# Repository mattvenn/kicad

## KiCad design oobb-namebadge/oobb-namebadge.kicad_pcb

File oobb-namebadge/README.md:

# OOBB compatible SAO V.1.69bis name badge

* compatible with OOBB https://github.com/oomlout/oomlout-OOBB/wiki/pictureIndex
* 5 x [SAO V.1.69bis](https://hackaday.com/2019/03/20/introducing-the-shitty-add-on-v1-69bis-standard/) 6 pin connectors - GPIO1&2 shared across all connectors. I2C not connected
* pads for LiPo battery and USB charger
* 90x70mm $5 USD from https://pcbway.com
* [iCEBreaker](https://www.crowdsupply.com/1bitsquared/icebreaker-fpga) compatible. Red and Green LED output drive GPIO1&2 on all SAOs.

# BOM

* J5019 LiPo booster incorporating [TC4056A](docs/TC4056A.pdf) LiPo charger
* LiPo battery measuring 46x52mm
* 3.3v regulator [LD1117S33TR](https://uk.farnell.com/stmicroelectronics/ld1117s33tr/v-reg-ldo-3-3v-smd-1117-sot-223/dp/1202826)
* 2 x 10k pullup resistors if using iCEBreaker to control GPIOs
* sliding SMT switch [JS102012SAQN](https://uk.farnell.com/c-k-components/js102011saqn/switch-spdt-0-6a-6vdc-side-smd/dp/2320017)
* 5 x female 2x3 pin header with 2.54mm spacing, eg this [Pololu part](https://www.pololu.com/product/1023)

# Gerbers & Schematic

* [docs/schematic.pdf](docs/schematic.pdf)
* [oobb-namebadge-2019-10-10-fab.zip](oobb-namebadge-2019-10-10-fab.zip)

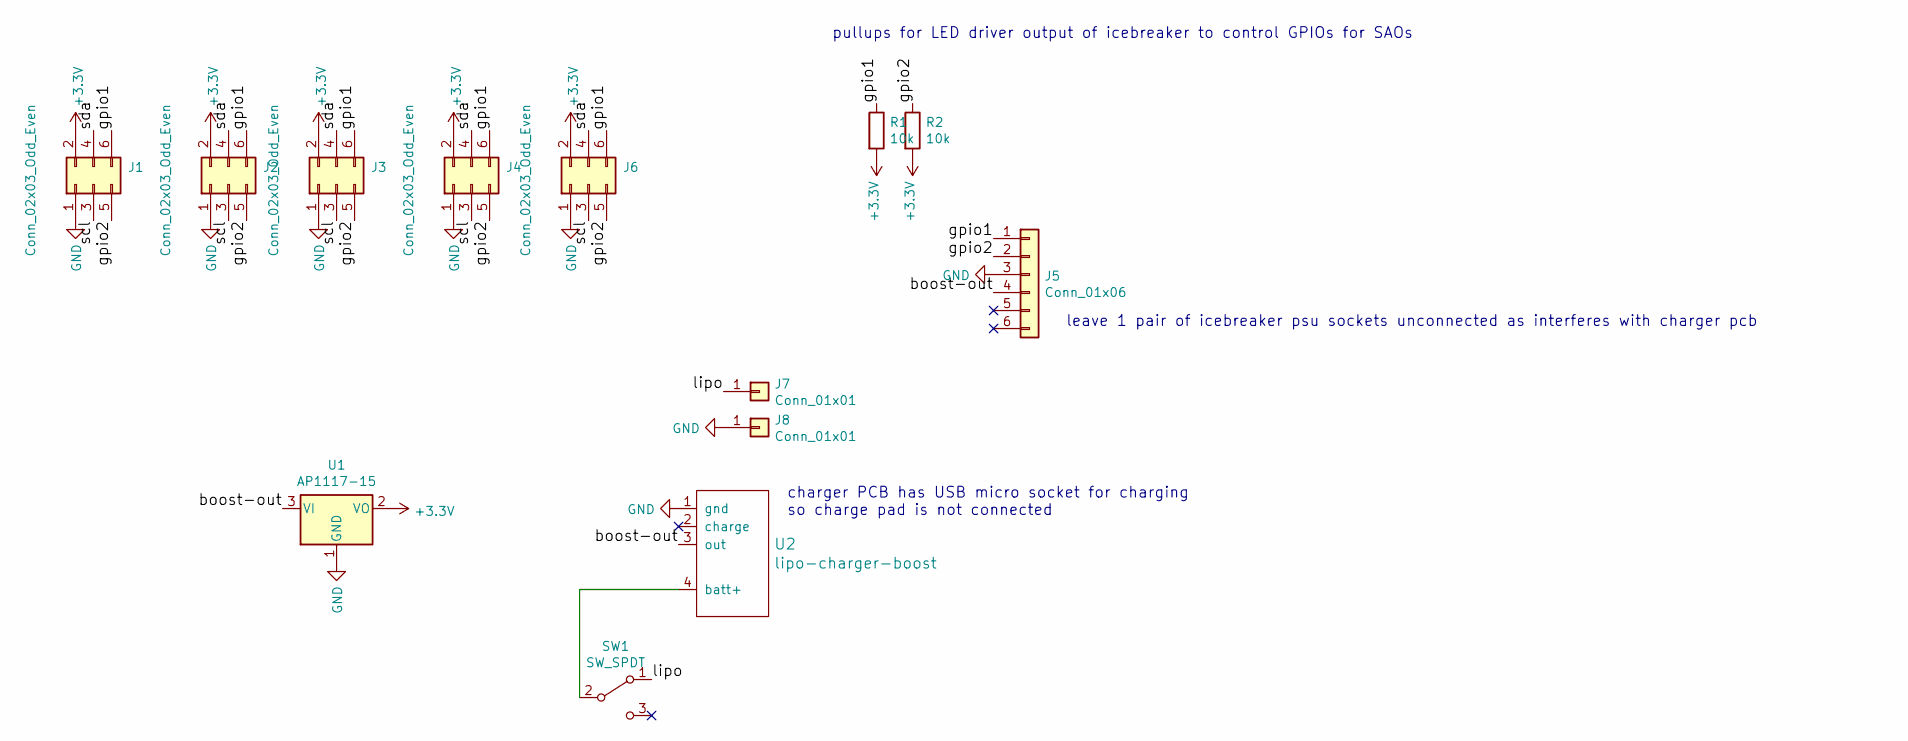
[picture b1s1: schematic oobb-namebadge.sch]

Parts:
J1, J2, J3, J4, J6: Conn_02x03_Odd_Even; Pin_Header_Straight_2x03_Pitch2.54mm
J5: Conn_01x06; icebreaker
J7, J8: Conn_01x01; Measurement_Point_Square-SMD-Pad_Big
R1, R2: 10k; R_0805_HandSoldering
SW1: SW_SPDT; SW_SPDT_CK-JS102011SAQN; farnell # 2320017
U1: AP1117-15; SOT-223; farnell # 1202826
U2: lipo-charger-boost

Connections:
+3V3: J1.2, J2.2, J3.2, J4.2, J6.2, R1.2, R2.2, U1.2 (VO)
/boost-out: J5.4, U1.3 (VI), U2.3 (out)
/gpio1: J1.6, J2.6, J3.6, J4.6, J5.1, J6.6, R1.1
/gpio2: J1.5, J2.5, J3.5, J4.5, J5.2, J6.5, R2.1
/lipo: J7.1, SW1.1 (A)
/scl: J1.3, J2.3, J3.3, J4.3, J6.3
/sda: J1.4, J2.4, J3.4, J4.4, J6.4
GND: J1.1, J2.1, J3.1, J4.1, J5.3, J6.1, J8.1, U1.1 (GND), U2.1 (gnd)
unnamed: SW1.2 (B), U2.4 (batt+)

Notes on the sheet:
charger PCB has USB micro socket for charging so charge pad is not connected
leave 1 pair of icebreaker psu sockets unconnected as interferes with charger pcb
pullups for LED driver output of icebreaker to control GPIOs for SAOs

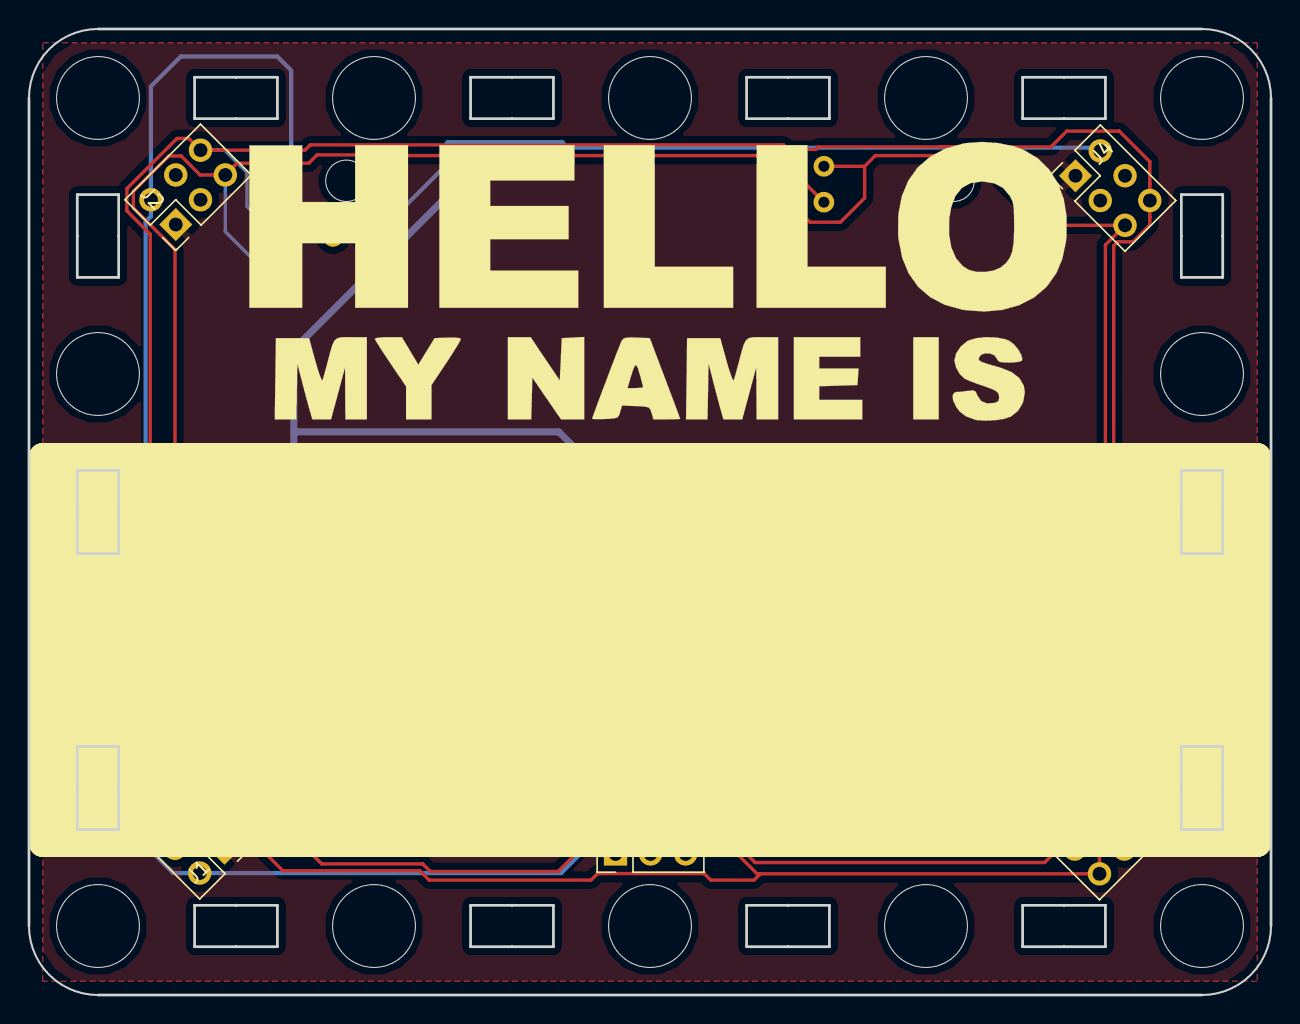
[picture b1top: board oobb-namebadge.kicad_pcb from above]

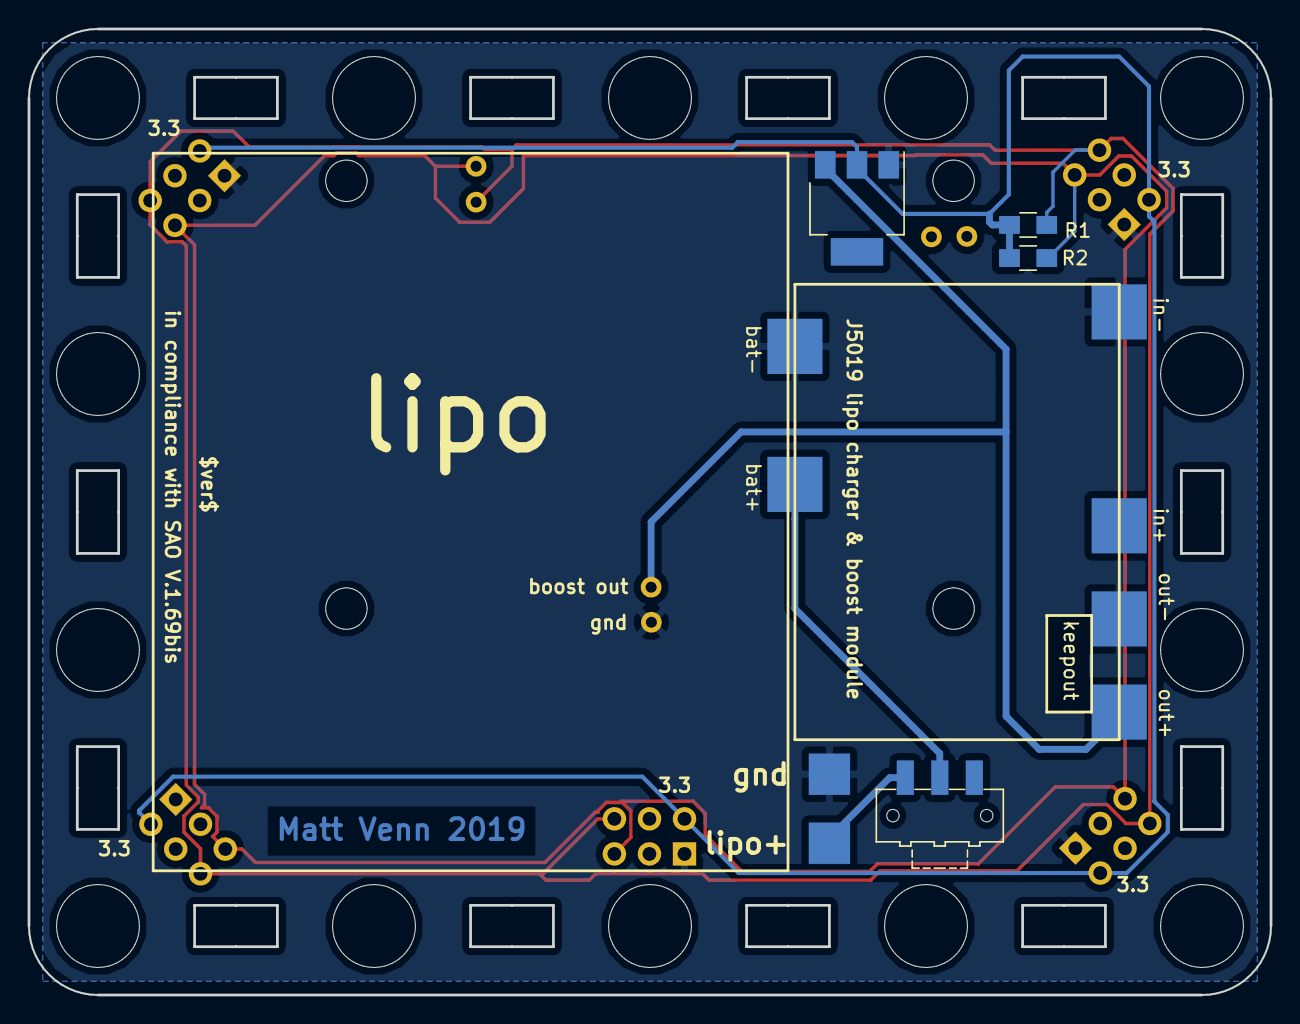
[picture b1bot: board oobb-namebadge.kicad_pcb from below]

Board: 2 copper layers, 90.0 x 70.0 mm, 13 parts (7 on the bottom side), 9 nets.

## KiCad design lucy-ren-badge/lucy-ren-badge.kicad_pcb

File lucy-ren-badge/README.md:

1300 dpi to convert from Rachel file to 71x51mm badge
$63 for 100 from pcbway

mask - normal then edit file to change layer
silk - invert
copper - invert then edit file
outline - fill black, export png, import inkscape, path->trace outline, scale 5.66, export DXF

reduced size of master image by 4 to 1008x756

BOM

pins - TODO!
slide switch - farnell
battery - ordered amazon
battery holder - farnell
attiny - check footprint & parts I have - done is correct
0.1u x 1  - farnell
1u x 1 - dnp
10k x 1 - farnell
60R x 1 - farnell

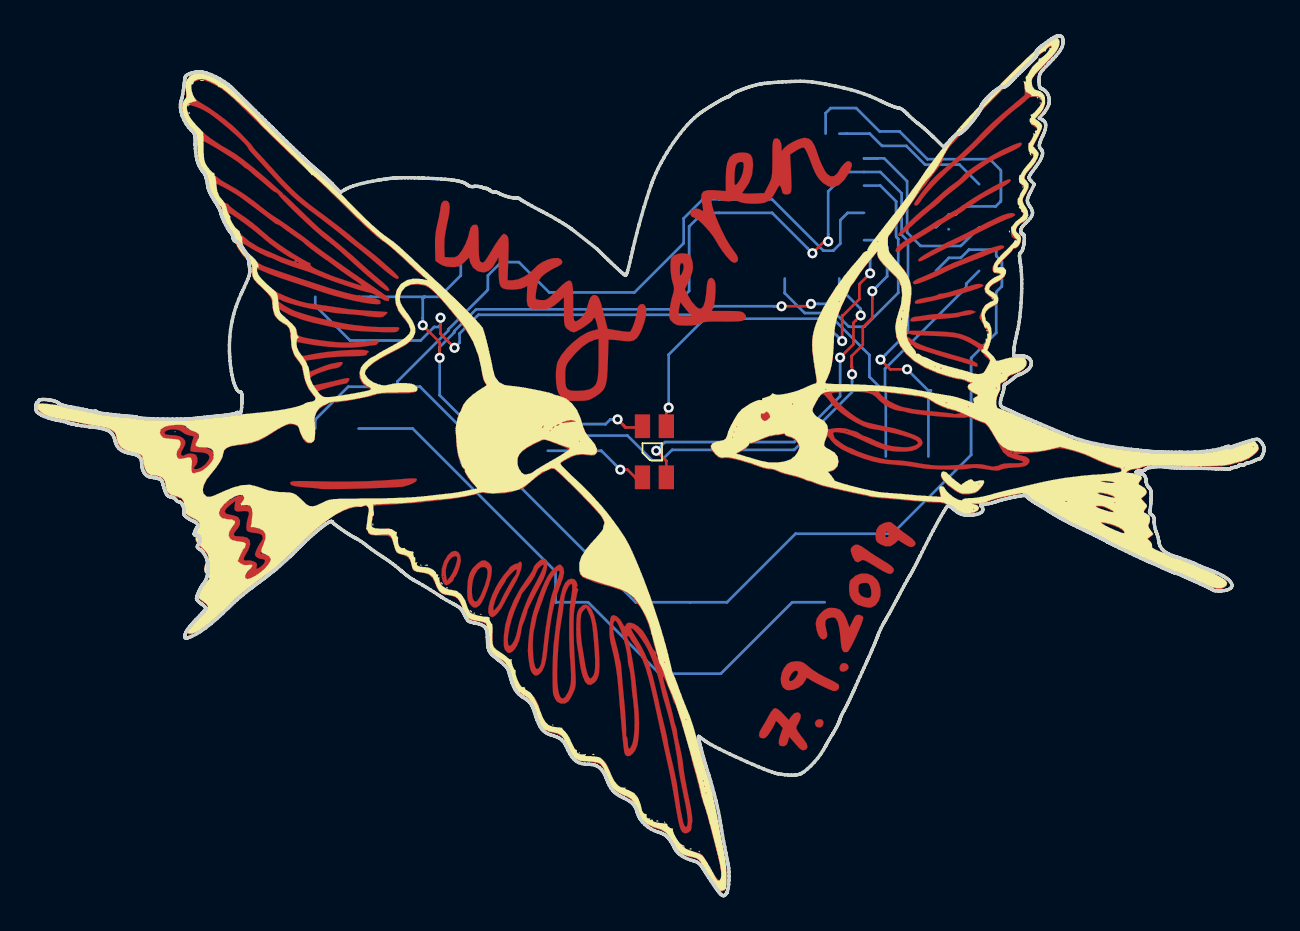
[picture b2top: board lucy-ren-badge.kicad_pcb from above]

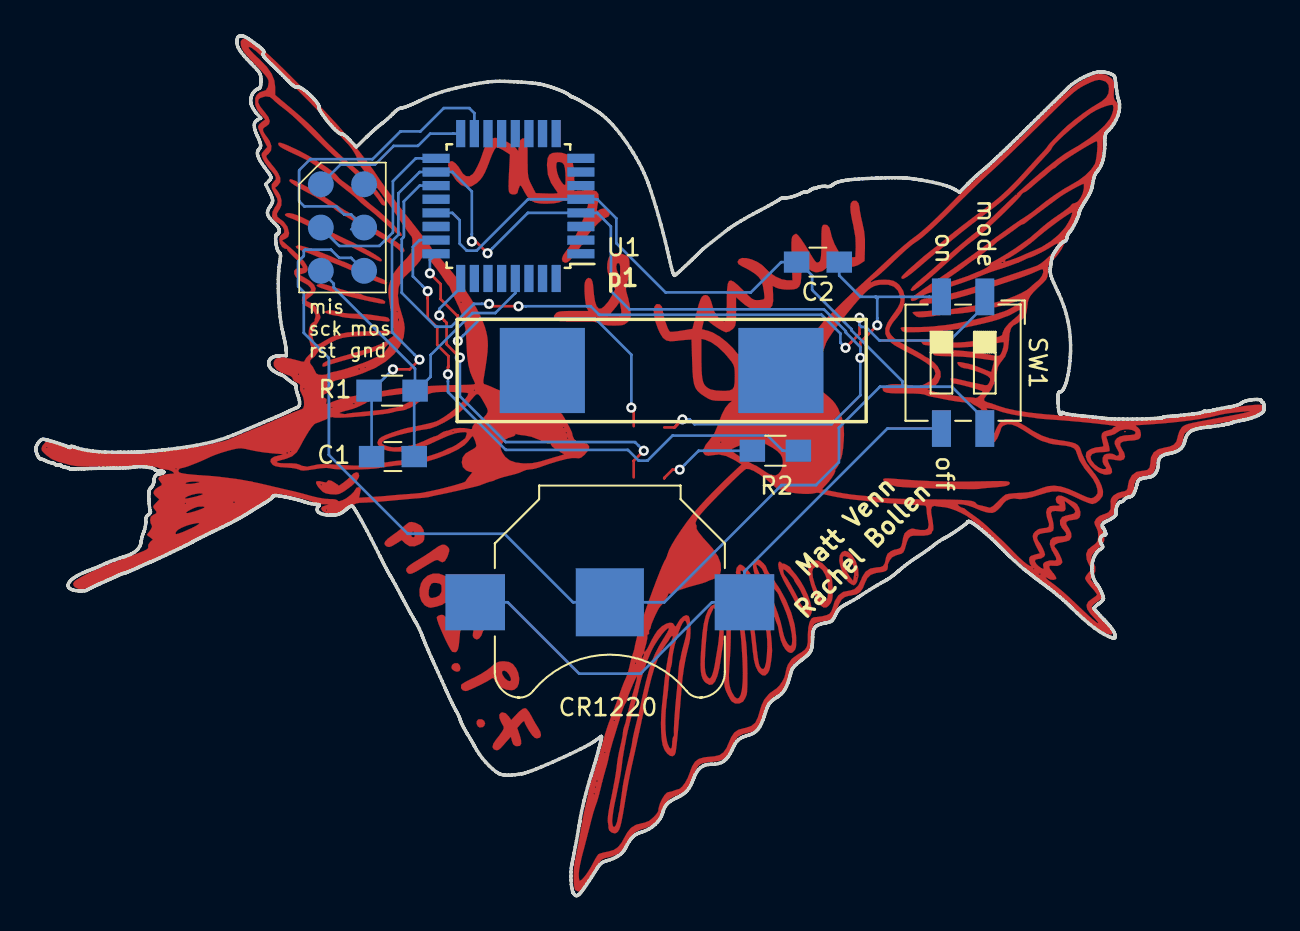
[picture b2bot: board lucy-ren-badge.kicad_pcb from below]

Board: 2 copper layers, 72.1 x 50.5 mm, 9 parts (8 on the bottom side), 12 nets.

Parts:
C1, C2: C; C_0805_HandSoldering
CR1220: Battery_Cell; Keystone_3000_1x12mm-CoinCell
J1: Conn_02x03_Odd_Even; icsp-2.54-smt
R1, R2: R; R_0805_HandSoldering
SW1: SW_DIP_x02; SW_DIP_SPSTx02_Slide_6.7x6.64mm_W6.73mm_P2.54mm_LowProfile_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
U1: ATTINY88-AU; TQFP-32_7x7mm_Pitch0.8mm
U2: rgbled; 3528-4p

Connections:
/b1: U1.25, U2.6
/g1: U1.24, U2.4
/miso: J1.1, U1.16
/mode: SW1.1, U1.19
/mosi: J1.4, U1.15
/r1: R2.2, U2.5
/reset: C1.2, J1.5, R1.1, U1.29
/sck: J1.3, U1.17
GND: C2.2, CR1220.2, J1.6, SW1.4, U1.5, U1.21
unnamed: CR1220.1, SW1.3
unnamed: R2.1, U1.23
VCC: C1.1, C2.1, R1.2, SW1.2, U1.4, U1.18, U2.1

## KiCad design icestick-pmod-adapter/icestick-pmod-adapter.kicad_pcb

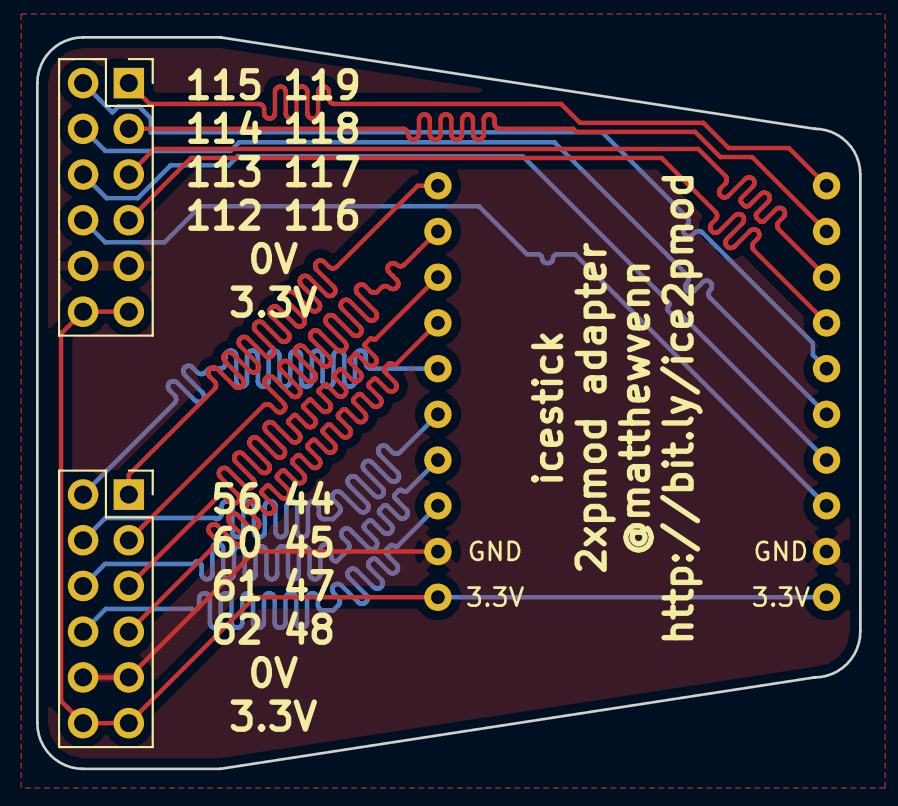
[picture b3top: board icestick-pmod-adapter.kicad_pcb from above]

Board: 2 copper layers, 45.7 x 40.6 mm, 3 parts (0 on the bottom side), 18 nets.

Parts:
J1, J2: Conn_02x06_Odd_Even; PinSocket_2x06_P2.54mm_Vertical
U1: icestick

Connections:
+3V3: J1.11, J1.12, J2.11, J2.12, U1.10, U1.20
/pmod44: J1.1, U1.1
/pmod45: J1.3, U1.2
/pmod47: J1.5, U1.3
/pmod48: J1.7, U1.4
/pmod56: J1.2, U1.5
/pmod60: J1.4, U1.6
/pmod61: J1.6, U1.7
/pmod62: J1.8, U1.8
/pmod112: J2.8, U1.18
/pmod113: J2.6, U1.17
/pmod114: J2.4, U1.16
/pmod115: J2.2, U1.15
/pmod116: J2.7, U1.14
/pmod117: J2.5, U1.13
/pmod118: J2.3, U1.12
/pmod119: J2.1, U1.11
GND: J1.9, J1.10, J2.9, J2.10, U1.9, U1.19

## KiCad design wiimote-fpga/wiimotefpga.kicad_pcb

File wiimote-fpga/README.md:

# breakout board for pixart IR camera used in wiimote

* PMOD interface.
* reset should be high for camera to run
* either use 25MHz onboard oscillator or supply 25MHz on clk pin

# bugs

* mixed sda and scl labels (fixed)
* crystal footprint was reversed (fixed)

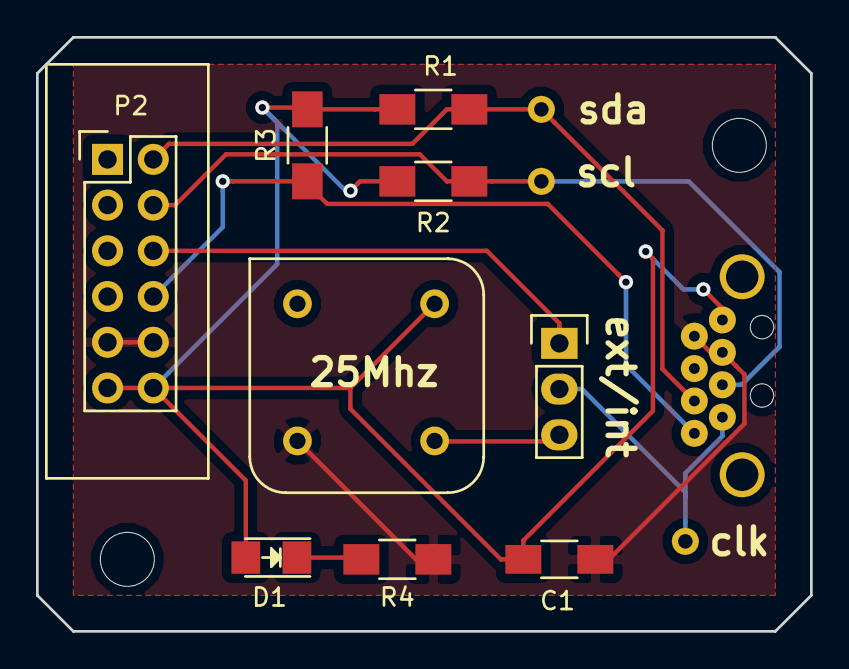
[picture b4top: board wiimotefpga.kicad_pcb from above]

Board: 2 copper layers, 43.0 x 33.0 mm, 13 parts (0 on the bottom side), 9 nets.

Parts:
C1: C; C_1206_HandSoldering
D1: LED; LED-1206
P1: CONN_01X03; Pin_Header_Straight_1x03
P2: CONN_02X06; Pin_Header_Straight_2x06
R1: R; R_1206_HandSoldering
R2: 4.7k; R_1206_HandSoldering
R3: 10k; R_1206_HandSoldering
R4: 150R; R_1206_HandSoldering
U1: oscillator
U2: wiimote-camera; wiimote
W1, W2, W3: TEST_1P; Measurement_Point_Round-TH_Small

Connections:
/cam_clk: P1.2, U2.7, W3.1
/clk: P1.1, P2.6
/osc: P1.3, U1.5
/reset: P2.8, R3.1, U2.8
/scl: P2.4, R2.1, U2.5, W2.1
/sda: P2.2, R1.1, U2.6, W1.1
GND: C1.2, P2.9, P2.10, R4.2, U1.4, U2.2, U2.3
unnamed: D1.1, R4.1
VCC: C1.1, D1.2, P2.11, P2.12, R1.2, R2.2, R3.2, U1.8, U2.1

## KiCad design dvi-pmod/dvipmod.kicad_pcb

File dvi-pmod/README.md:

# Minimal PMOD to DVI-D adapter

For FPGAs with no TMDS, trying to use AC coupled LVDS.
AC coupling suggested in this discussion:

http://electronics.stackexchange.com/questions/130942/transmitting-hdmi-dvi-over-an-fpga-with-no-support-for-tmds

# Status

* tested pattern at 640 x 480 @ 60Hz
* total pixels is 800 x 525 @ 60Hz = 25.2Mhz = 39.6ns

[pictures](https://goo.gl/photos/ScRRi142sbwstPGr6)

# Schematic

# Board

# Todo

* too close trace to g resistor, bridged when soldering

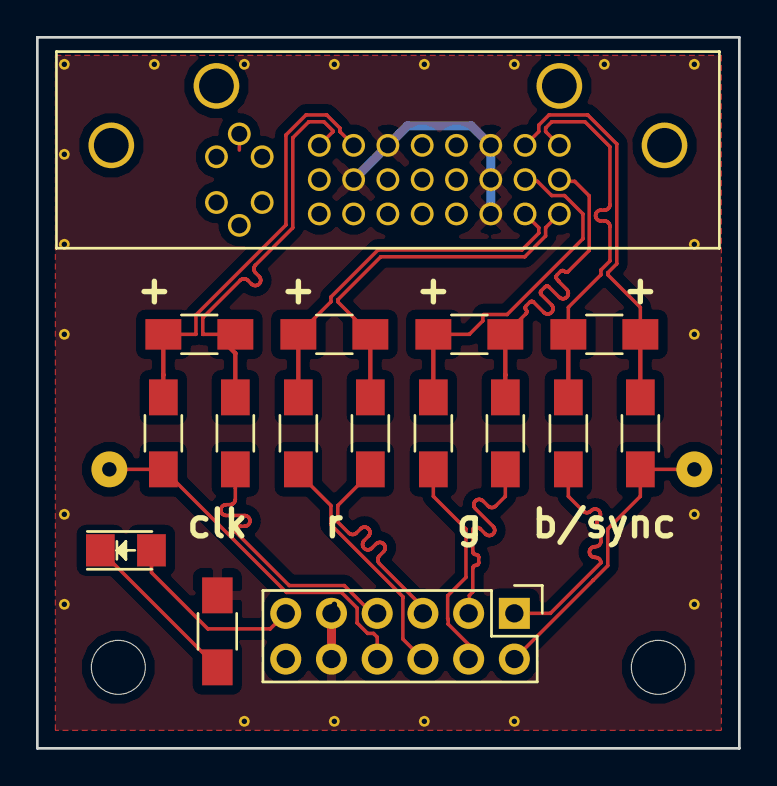
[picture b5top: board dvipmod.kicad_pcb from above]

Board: 2 copper layers, 39.0 x 39.5 mm, 18 parts (0 on the bottom side), 19 nets.

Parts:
C1, C2, C3, C4, C5, C6, C7, C8: C; C_1206_HandSoldering
D1: LED; LED-1206
P1: CONN_02X06; Pin_Header_Straight_2x06
R1, R2, R3, R4, R5: R; R_1206_HandSoldering
U1: dvi; molex dvi ra
W6, W8: TEST_1P; SolderWirePad_single_0-8mmDrill

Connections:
/b+: C6.2, P1.2, W6.1
/b-: C5.2, P1.1
/blue+: C6.1, R3.2, U1.18
/blue-: C5.1, R3.1, U1.17
/c+: C8.2, P1.8, W8.1
/c-: C7.2, P1.7
/clock+: C8.1, R4.2, U1.23
/clock-: C7.1, R4.1, U1.24
/g+: C4.2, P1.4
/g-: C3.2, P1.3
/green+: C4.1, R2.2, U1.10
/green-: C3.1, R2.1, U1.9
/r+: C2.2, P1.6
/r-: C1.2, P1.5
/red+: C2.1, R1.2, U1.2
/red-: C1.1, R1.1, U1.1
Earth: P1.9, P1.10, R5.2, U1.3, U1.11, U1.15, U1.19, U1.22
unnamed: D1.1, R5.1
VCC: D1.2, P1.11, P1.12

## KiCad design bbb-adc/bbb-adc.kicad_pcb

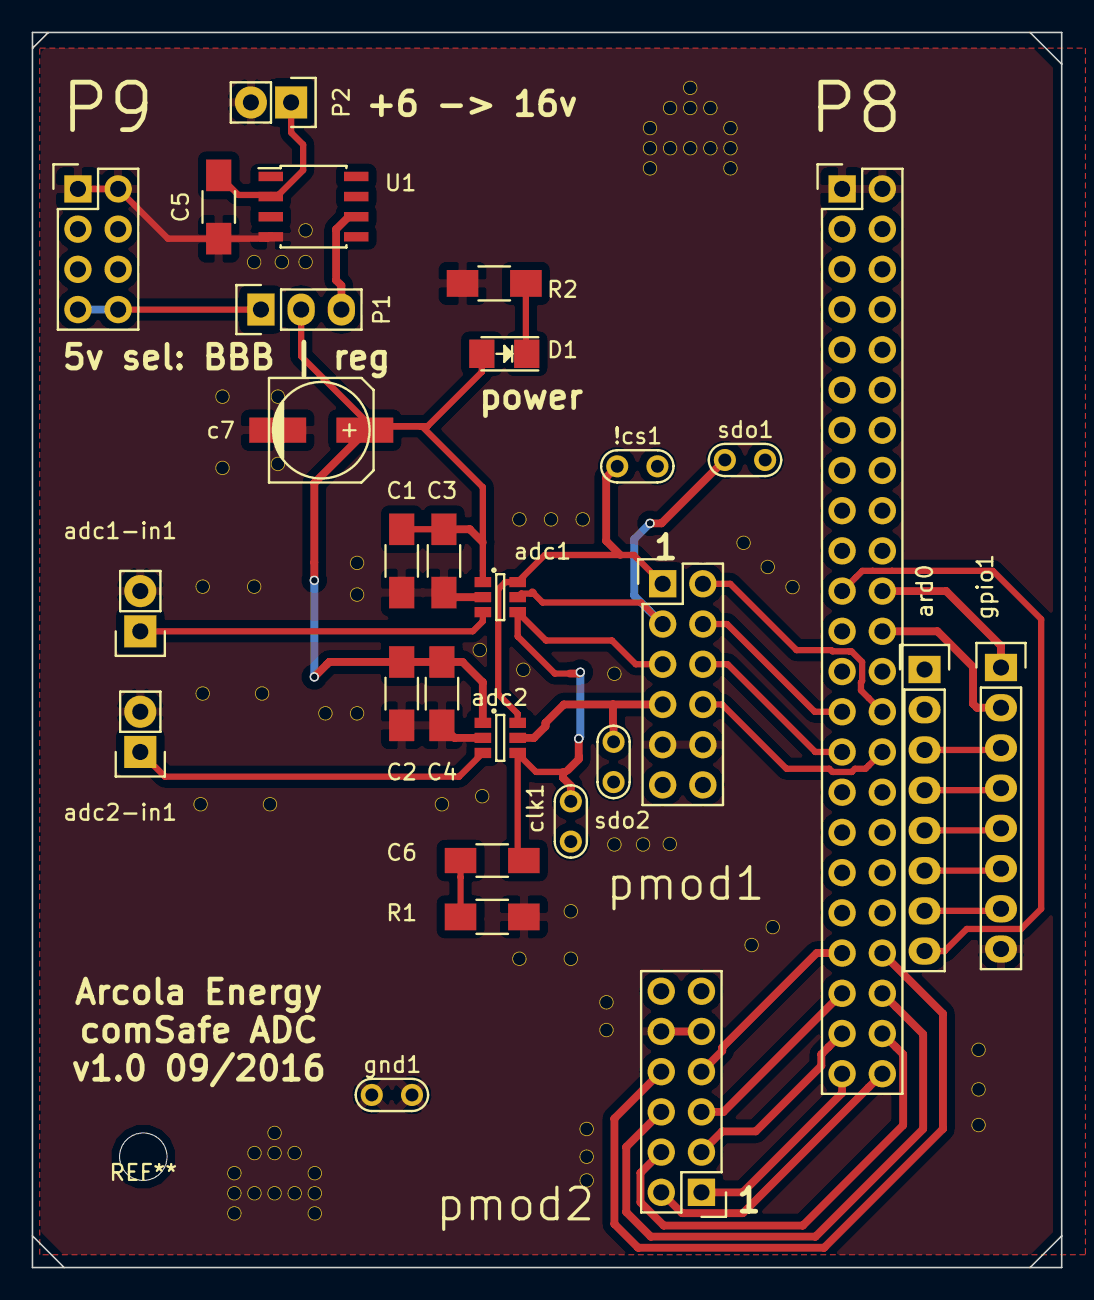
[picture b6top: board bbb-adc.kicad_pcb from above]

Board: 2 copper layers, 65.0 x 78.0 mm, 28 parts (0 on the bottom side), 33 nets.

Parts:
!cs1: TEST; Test_Point
C1, C2, C5: 1u; C_1206_HandSoldering
C3, C4: 10n; C_1206_HandSoldering
C6: 1nf; C_1206_HandSoldering
D1: LED; LED-1206
P1: CONN_01X03; Pin_Header_Straight_1x03
P2: CONN_01X02; Pin_Header_Straight_1x02
P8: CONN_02X23; Pin_Header_Straight_2x23
P9: CONN_02X04; Pin_Header_Straight_2x04
R1: 100R; R_1206_HandSoldering
R2: R; R_1206_HandSoldering
U1: ref5050; SOIC-8_3.9x4.9mm_Pitch1.27mm
adc1, adc2: ads7883; SOT-23-6
adc1-in1, adc2-in1: CONN_01X02; Pin_Header_Straight_1x02
ard0: CONN_01X08; Pin_Header_Straight_1x08
c7: 22u; c_elec_6.3x7.7
clk1: TEST; Test_Point
gnd1: TEST; Test_Point
gpio1: CONN_01X08; Pin_Header_Straight_1x08
pmod1, pmod2: CONN_02X06; Pin_Header_Straight_2x06
sdo1, sdo2: TEST; Test_Point

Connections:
+12V: C5.1, P2.1, U1.2
/bit0: P8.45, pmod2.1
/bit1: P8.46, pmod2.2
/bit2: P8.43, pmod2.3
/bit3: P8.44, pmod2.4
/bit4: P8.41, pmod2.5
/bit5: P8.42, pmod2.6
/bit6: P8.39, pmod2.7
/bit7: P8.40, pmod2.8
/bit8: P8.27, pmod1.4
/bit9: P8.29, pmod1.6
/bit10: P8.28, pmod1.2
/bit11: P8.30, pmod1.8
Earth: C1.2, C2.2, C3.2, C4.2, C5.2, P2.2, P8.1, P8.2, P9.1, P9.2, R1.1, R2.2, U1.4, adc1.2, adc1-in1.2, adc2.2, adc2-in1.2, c7.2, gnd1.1, gpio1.8, pmod1.9, pmod1.10, pmod2.9, pmod2.10
unnamed: C6.2, R1.2
unnamed: D1.1, R2.1
unnamed: adc1.3, adc1-in1.1
unnamed: adc2.3, adc2-in1.1
unnamed: ard0.3, gpio1.3
unnamed: ard0.4, gpio1.4
unnamed: ard0.5, gpio1.5
unnamed: ard0.6, gpio1.6
unnamed: ard0.7, gpio1.7
adc1-sdo: adc1.5, pmod1.3, sdo1.1
adc2-sdo: adc2.5, pmod1.7, sdo2.1
adc-5v: C1.1, C2.1, C3.1, C4.1, D1.2, P1.2, adc1.1, adc2.1, c7.1
adc-clk: C6.1, adc1.4, adc2.4, clk1.1, pmod1.5
adc-cs: !cs1.1, adc1.6, adc2.6, pmod1.1
bbb-5v: P1.1, P9.7, P9.8
gpio1: P8.22, gpio1.1
gpio2: P8.24, gpio1.2
pru-ready: P8.21, ard0.8
ref-5v: P1.3, U1.6

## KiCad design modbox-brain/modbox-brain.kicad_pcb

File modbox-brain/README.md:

# schematic

[pdf](schematic.pdf)

# power consideration

ESP8266 uses about 100ma when on with wifi
lcd board will use about 50ma
knobs with all leds will use about 100ma with 5ma led current
guess that buttons will be about half knobs = 50ma (less leds)

2 lcds + 2 knobs + button + brain = 450ma max, easy to imagine something twice
as big, so supply should provide 100ma to 1000ma.

Initial idea was to use an LDO with enable as with lipo this will provide
between 80 & 90% efficiency. However, as unit may run continuously on 5v,
efficiency drops to 70%. Switched to using a [TI LMR10510 buck
regulator](http://www.ti.com/lit/ds/symlink/lmr10510.pdf), which should provide
90%, though datasheet doesn't show how efficiency varies with changing input
voltage.

# states & indicators

    off -> on with vusb -> vusb goes off -> timeout -> off
    off -> on with battery -> timeout -> off

## off

lowest power, no indicators

## plugged in with usb

immediate indicator that plugging in has worked, either:

* red charge led shows charging, or
* green charge complete led shows charge complete

## on

immediate indicator of on-ness via blue status led:

* comes on asap to show system is working. 
* pulses low while wifi connects, goes off when wifi connected
* flashes whenever mqtt messages exchanged

## with battery low

indicator of battery low with separate red led:

* getting low, flash
* too low, on

# IO for power management

inputs:

* vusb via divider
* vbat adc via enable mosfet

outputs:

* enable output for adc enable and reg enable
* low batt led

# esp8266 flash with nodemcu style gpio control

* gpio15 must be low, gpio2 must be high
* gpio0 high -> run mode
* gpio0 low -> flash mode
* gpio16 tied to reset for sleep mode wake up

cp2102 dtr & rts control 2 transistors that control reset and gpio0

Tested by building transistor circuit copied from nodemcu schematic esp12 v0.9
20/11/2014.

boardtype in arduino is nodemcu 0.9 (uses nodemcu for board type with esptool)

tested with cp1202 chip on breakout
[tests results](esp-prog-test/nodemcu-results) = 18/20 success

serial output works too

## usb current settings 

able to set max current to cp2102 with [this tool]
(https://github.com/Lembed/Usb-Serial-Breakout-Cp2102)

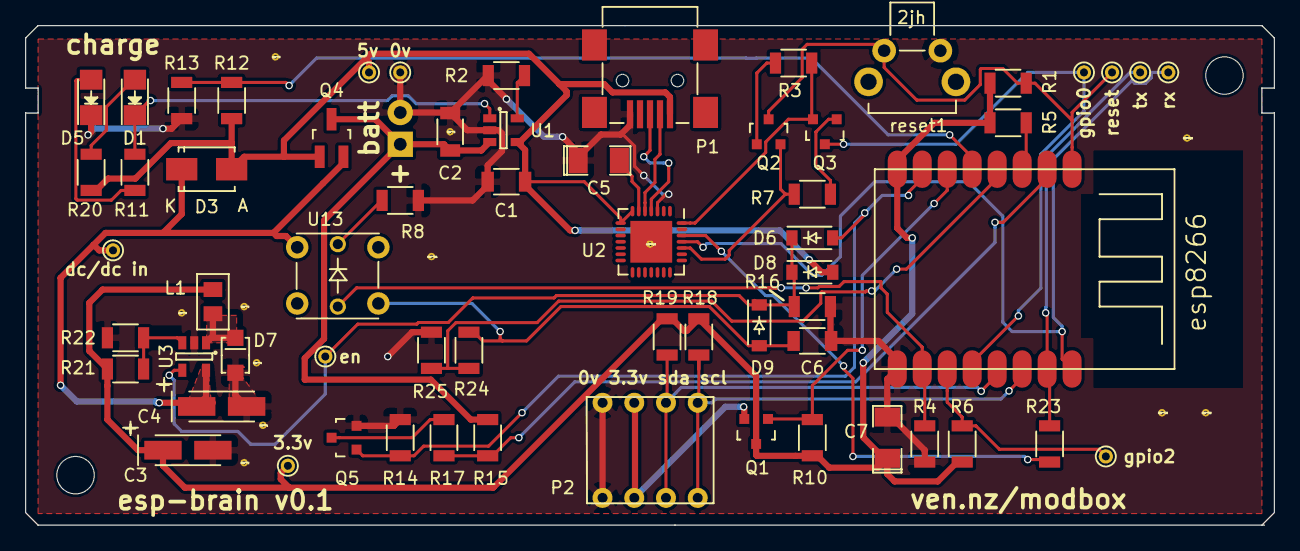
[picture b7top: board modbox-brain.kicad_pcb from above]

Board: 2 copper layers, 100.0 x 40.0 mm, 63 parts (1 on the bottom side), 38 nets.

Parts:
C1, C2: 4.7u; C_1206
C3: 22uf 5v; TantalC_SizeA_EIA-3216_HandSoldering
C4: 22uf 10v; TantalC_SizeA_EIA-3216_HandSoldering
C5, C7: 0.1uf; SMD-1206_Pol
C6: 1u; C_1206
D1: charging led; LED-1206
D3: D_Schottky; SMA_Standard
D5: charge complete led; LED-1206
D6, D8, D9: D; SOD-123
D7: 1.5a; sod-123w
L1: 2.2u 1.8A; CC08CC
P1: MICRO-USB-B; usb-mini-b
P2: CONN_01X04; molex 4way cgrid
Q1: Q_PMOS_GDS; SOT-23
Q2, Q3: BC849; SOT-23
Q4: Q_PMOS_GSD; SOT-23_Handsoldering
Q5: Q_NMOS_GSD; SOT-23
R1, R3, R4, R5, R6, R7, R14, R17: 10k; R_1206
R2: 2k; R_1206
R8: 68r; R_1206
R10, R16, R22: 100k; R_1206
R11, R20: 500r; R_1206
R12, R24: 30k; R_1206
R13, R25: 60k; R_1206
R15, R18, R19: 4.7k; R_1206
R21: 45.3k; R_1206
R23: 470r; R_1206
U1: MCP73831; SOT-23-5
U2: CP2102; QFN-28-1EP_5x5mm_Pitch0.5mm
U3: lmr10510; SOT-23-5
U4, U5, U6, U7, U8, U9, U10, U11, U12, U14: testpoint; PINTST
U13: TLL-62
batt1: CONN_01X02; Pin_Header_Straight_1x02
esp8266: U2; esp8266-12
reset1: SW_PUSH; ra tactile

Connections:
+3V3: C3.1, C7.1, L1.2, Q1.3, R1.1, R4.1, R5.1, R10.1, R18.1, R19.1, R21.1, U10.1, esp8266.8
+5V: C1.1, D3.2, D8.2, P1.1, Q4.1, R11.2, R12.2, U1.4, U2.7, U2.8, U9.1
/D+: P1.3, U2.4
/D-: P1.2, U2.5
/bus-power: P2.2, Q1.2
/ch_pd: R5.2, esp8266.3
/charger/dcdc-in: C4.1, D3.1, Q4.2, U3.5, U12.1, U13.4
/charger/enable: D6.1, D8.1, D9.1, R16.1, U3.4, U8.1
/charger/fb: R21.2, R22.1, U3.3
/charger/sw: D7.1, L1.1, U3.1
/gpio0: Q3.3, U4.1, esp8266.12
/gpio2: R4.2, U14.1, esp8266.11
/i2c-bus-power: Q1.1, R10.2, esp8266.6
/reset: Q2.3, R1.2, U5.1, esp8266.1, reset1.2
/scl: P2.4, R18.2, esp8266.14
/sda: P2.3, R19.2, esp8266.13
GND: C1.2, C2.2, C3.2, C4.2, C5.1, C6.2, C7.2, D5.1, D7.2, P1.5, P2.1, Q5.2, R2.2, R6.2, R8.1, R13.1, R14.2, R16.2, R22.2, R25.1, U1.2, U2.3, U3.2, U11.1, batt1.2, esp8266.9, reset1.1
unnamed: C5.2, U2.6
unnamed: C6.1, D9.2, R24.2, U13.1
unnamed: D1.1, R20.2, U1.1
unnamed: D1.2, R11.1
unnamed: D5.2, R20.1
unnamed: Q2.1, R3.2
unnamed: Q3.1, R7.2
unnamed: Q5.3, R17.2
unnamed: R2.1, U1.5
unnamed: R8.2, U13.5
unnamed: R23.2, U2.26
adc: R15.2, R17.1, esp8266.2
batt: C2.1, Q4.3, R15.1, U1.3, batt1.1
button: R24.1, R25.2, esp8266.4
dtr: Q3.2, R3.1, U2.28
gpio15: R6.1, U13.6, esp8266.10
power-on: D6.2, Q5.1, R14.1, esp8266.7
rts: Q2.2, R7.1, U2.24
rx: U2.25, U6.1, esp8266.16
tx: R23.1, U7.1, esp8266.15
usb-on: R12.1, R13.2, esp8266.5

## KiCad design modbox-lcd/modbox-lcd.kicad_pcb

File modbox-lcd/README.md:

fixes for v1.1

pot is connected wrong
holes too small for lcd

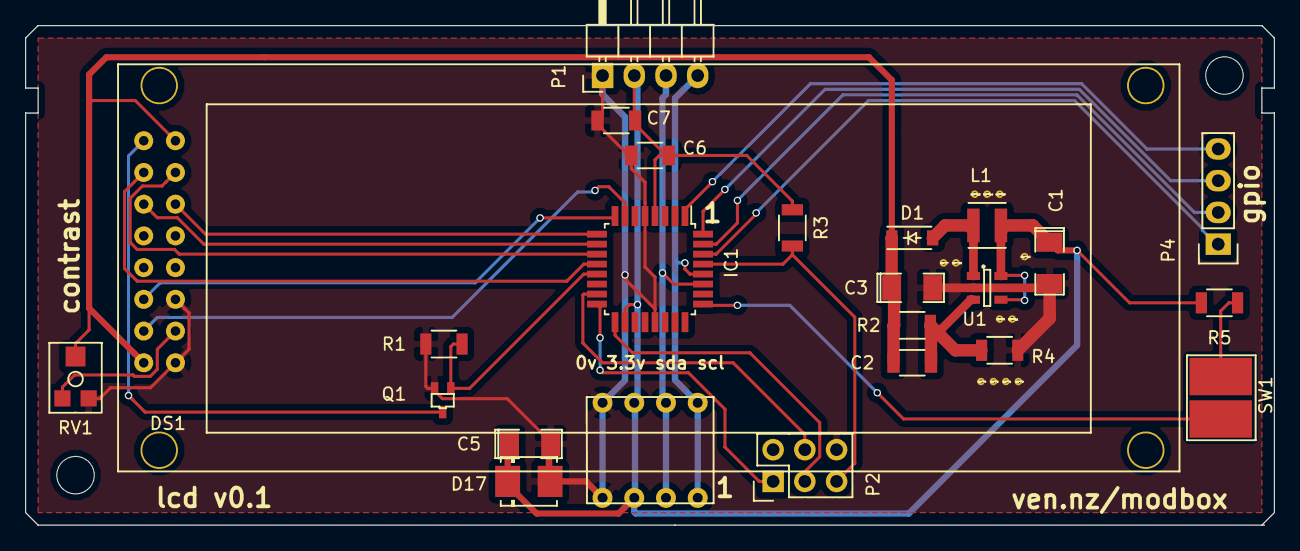
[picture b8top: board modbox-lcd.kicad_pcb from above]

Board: 2 copper layers, 100.0 x 40.0 mm, 24 parts (0 on the bottom side), 26 nets.

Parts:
C1, C3: 4.7u; SMD-1206_Pol
C2: 3.3pf; C_1206
C5: 10u; SMD-1206_Pol
C6: 0.1u; C_1206
C7: 1u; C_1206
D1: D_Schottky; SOD-123
D17: 1A; DO-214BA
DS1: LCD-016N002L; lcd-endconn
IC1: ATTINY88-A; TQFP-32_7x7mm_Pitch0.8mm
L1: 3.3u; Neosid_Inductor_SMS-ME3015
P1: CONN_01X04; Pin_Header_Angled_1x04
P2: CONN_02X03; Pin_Header_Straight_2x03
P3: CONN_01X04; molex 4way cgrid
P4: CONN_01X04; Pin_Header_Straight_1x04
Q1: MMBF170; SOT-323
R1: 10k; R_1206
R2: 620k; R_1206
R3: 20k; R_1206
R4: 200k; R_1206
R5: 1m; R_1206
RV1: POT; 3mm pot
SW1: SW_PUSH; button
U1: tps61040; SOT-23-5

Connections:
+3V3: C1.1, C5.1, C6.1, C7.1, D17.1, IC1.4, IC1.18, L1.1, P1.2, P3.2, R3.1, R5.1, U1.4, U1.5
+5V: C2.1, C3.1, D1.1, DS1.2, DS1.15, R2.1, RV1.3
Earth: C1.2, C3.2, C5.2, C6.2, C7.2, D17.2, DS1.1, DS1.5, IC1.5, IC1.21, P1.1, P2.6, P3.1, Q1.2, R1.2, R4.2, RV1.1, U1.2
unnamed: C2.2, R2.2, R4.1, U1.3
unnamed: D1.2, L1.2, U1.1
unnamed: DS1.3, RV1.2
unnamed: DS1.16, Q1.3
unnamed: IC1.1, P4.4
unnamed: IC1.30, P4.1
unnamed: IC1.31, P4.2
unnamed: IC1.32, P4.3
unnamed: R5.2, SW1.2
butt: IC1.25, SW1.1
d4: DS1.11, IC1.9
d5: DS1.12, IC1.10
d6: DS1.13, IC1.11
d7: DS1.14, IC1.12
en: DS1.6, IC1.8
miso: IC1.16, P2.1
mosi: IC1.15, P2.4
pwm: IC1.13, Q1.1, R1.1
reset: IC1.29, P2.5, R3.2
rs: DS1.4, IC1.7
sck: IC1.17, P2.3
scl: IC1.28, P1.4, P3.4
sda: IC1.27, P1.3, P3.3

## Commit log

2015-07-13 esp breakout
2015-07-17 all libs inside project
2015-07-17 moved libs
2015-07-17 libs in one place
2015-07-20 esp12 breakout
2015-07-20 temp sensor board for esp8266
2015-07-20 notes
2015-07-22 logo
2015-07-24 better pin ordering
2015-07-25 sent to fab
2015-07-25 fixed gpio 4/5 mixup
2015-07-25 my library
2015-07-25 libs
2015-07-25 trying to unify libs
2015-07-26 added reset pin to breakout for deepsleep
2015-08-03 notes on adding footprints and symbols
2015-08-08 adapted for kicad export
2015-08-11 removed rescue lib
2015-08-17 added bom
2015-08-20 4&5 pin flip bug
2015-09-01 added header part #
2015-09-01 serial silk screen and v2
2015-09-01 swapped gpio 4&5
2015-09-01 swapped gpio4&5
2015-09-14 workshop doc
2015-09-14 schematic
2015-09-14 adding libs
2015-09-14 layout pic
2015-09-14 edits
2015-09-20 renamed
2015-09-20 moved all up a directory
2015-09-20 barrel jack lib
2015-09-20 barrel lib
2015-09-20 checked 7805 package
2015-09-25 printing
2015-11-02 earth to mars pibot sense board
2015-11-02 flying lead configuration
2015-11-02 fixed mosfet fp and added header for vbat=vcc
2015-11-03 component values
2015-11-03 switched pins for working PWM, aligned header for direct connection
2015-11-03 added cap
2015-11-06 adapted to take farnel #
2015-11-06 bom info
2015-11-06 added quant field
2015-11-06 better comment
2015-12-08 mq8 sensor board
2016-04-19 v3 added pull up resistors for gpio0 & 2
2016-09-07 mostly tested pcb2gcode settings
2016-09-07 drill was slightly too short, outline milling too narrow bit
2016-09-07 inc track width, connect extra bbb to gpio, via size and ground stitching
2016-09-12 fab to oshpark
2016-09-20 pcb & schematic
2016-09-20 fixed all the pcb mistakes
2016-09-20 fixed gpio boot issues
2016-10-05 sent to dirty pcb
2016-10-06 adjustments
2016-10-07 rev conn diode, smaller caps, cleaner layout, wider slots
2016-10-07 new fab
2016-10-07 fixed miso/mosi mixup
2016-10-14 first commit for modbox-lcd
2016-10-21 new footprints, dc boost tested, ready for fab
2016-10-21 molex fp
2016-10-22 first draft schematic & layout
2016-10-22 fixed lib
2016-10-25 charger
2016-10-27 charger and leds
2016-10-27 current considerations
2016-10-28 tofab
2016-11-01 buck converter instead of ldo
2016-11-01 schematic and notes update
2016-11-01 buck comments
2016-11-04 fps for switcher
2016-11-05 smaller diode
2016-11-17 component update before order
2016-11-24 fixes
2016-12-15 first round of fixes post fab
2016-12-30 added farnell #;
2017-02-03 pmod to dvi first commit
2017-02-22 notes - working!
2017-05-12 api test with python
2017-05-12 added links
2017-06-10 wiimote camera breakout
2017-11-07 add git version and date to pcb
2017-11-13 etch notes
2018-02-20 auto pcb exporting
2018-02-20 config for export_pcb.py
2018-02-20 readme updated for export_pcb.py
2018-03-13 add git repo version, better error message
2018-03-21 farnell bom
2018-03-21 handle different column orderings
2018-03-21 update after installing on Guillems pc
2018-06-12 step export
2018-07-02 skip row if supplier is DNP
2018-07-02 bug in not returning from function
2018-07-02 git version on board
2018-07-31 config
2018-07-31 added bitlink
2018-11-15 add $git$ and $date$ for only git or date strings
2019-08-23 commit before order
2019-08-23 add note about pins
2019-08-23 track spacing
2019-08-23 mask notes
2019-08-23 add Rachel
2019-08-24 manual gerber export
2019-09-03 removed lucy badge
2019-10-03 oobb badge
2019-10-03 needs lipo charger
2019-10-08 added icebreaker, ldo, switch and boost board
2019-10-10 fp files
2019-10-10 docs
2019-10-10 move images to docs
2019-10-10 ready to fab
2019-10-10 fixed missing silk poly
2019-10-10 battery charger ic
2019-10-10 added fab files
2019-10-10 add pics
2019-10-10 readme
2019-10-10 parts
2019-10-10 fix 2x6
2019-10-10 schematic and gerber links
2019-10-10 layout
2020-01-12 fixes for python3
2020-02-18 python3
